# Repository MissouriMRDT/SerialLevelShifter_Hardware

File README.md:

# SerialLevelShifter_Hardware
A 3.3V to 5V level shifter

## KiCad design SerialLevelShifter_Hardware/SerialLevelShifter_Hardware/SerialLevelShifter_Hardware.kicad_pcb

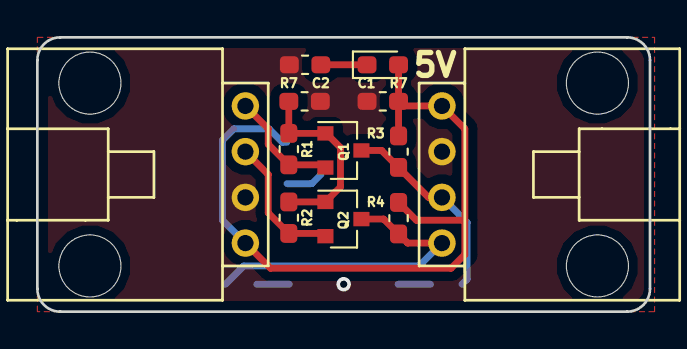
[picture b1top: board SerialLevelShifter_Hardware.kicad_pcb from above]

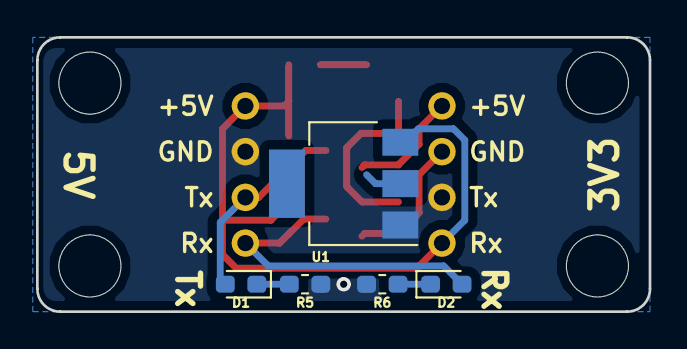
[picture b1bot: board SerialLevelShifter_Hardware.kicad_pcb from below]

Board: 2 copper layers, 34.0 x 15.2 mm, 17 parts (5 on the bottom side), 10 nets.

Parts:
C1, C2: 10u; C_0603_1608Metric_Pad1.05x0.95mm_HandSolder
Conn1, Conn2: Molex_SL_04; MOLEX_SL_04_Horizontal
D1, D2: LED; LED_0603_1608Metric_Pad1.05x0.95mm_HandSolder
Q1, Q2: BSS138; SOT-23
R1, R2, R3, R4: 10K; R_0603_1608Metric_Pad1.05x0.95mm_HandSolder
R5, R6, R7#2: 500; R_0603_1608Metric_Pad1.05x0.95mm_HandSolder
R7: LED; LED_0603_1608Metric_Pad1.05x0.95mm_HandSolder
U1: AZ1117-3.3; SOT-223

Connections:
3V3_Rx: Conn1.4, Q1.2, R1.2
3V3_Tx: Conn1.3, Q2.2, R2.2
5V_Rx: Conn2.4, D2.2, Q2.3, R4.2
5V_Tx: Conn2.3, D1.2, Q1.3, R3.2
+3V3: C2.1, Q1.1, Q2.1, R1.1, R2.1, U1.2
+5V: C1.1, Conn1.1, Conn2.1, R3.1, R4.1, R7.2, U1.3
GND: C1.2, C2.2, Conn1.2, Conn2.2, R5.2, R6.2, R7#2.2, U1.1
unnamed: D1.1, R5.1
unnamed: D2.1, R6.1
unnamed: R7.1, R7#2.1

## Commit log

2019-11-22 Started schematic
2019-11-23 preliminary layout
2019-11-23 finished layout
